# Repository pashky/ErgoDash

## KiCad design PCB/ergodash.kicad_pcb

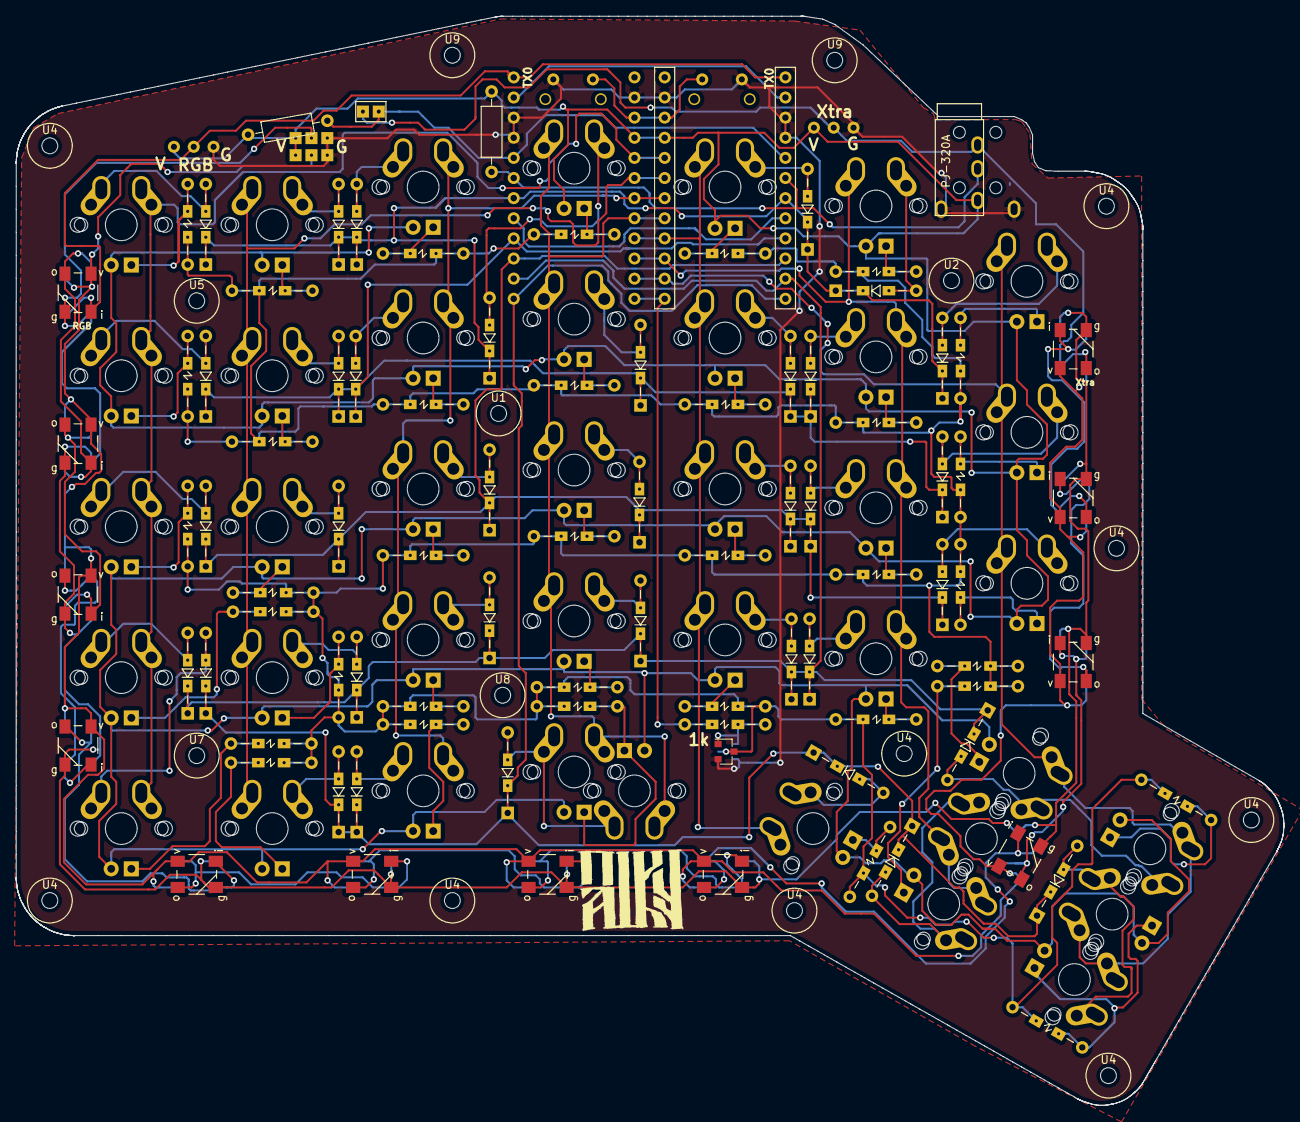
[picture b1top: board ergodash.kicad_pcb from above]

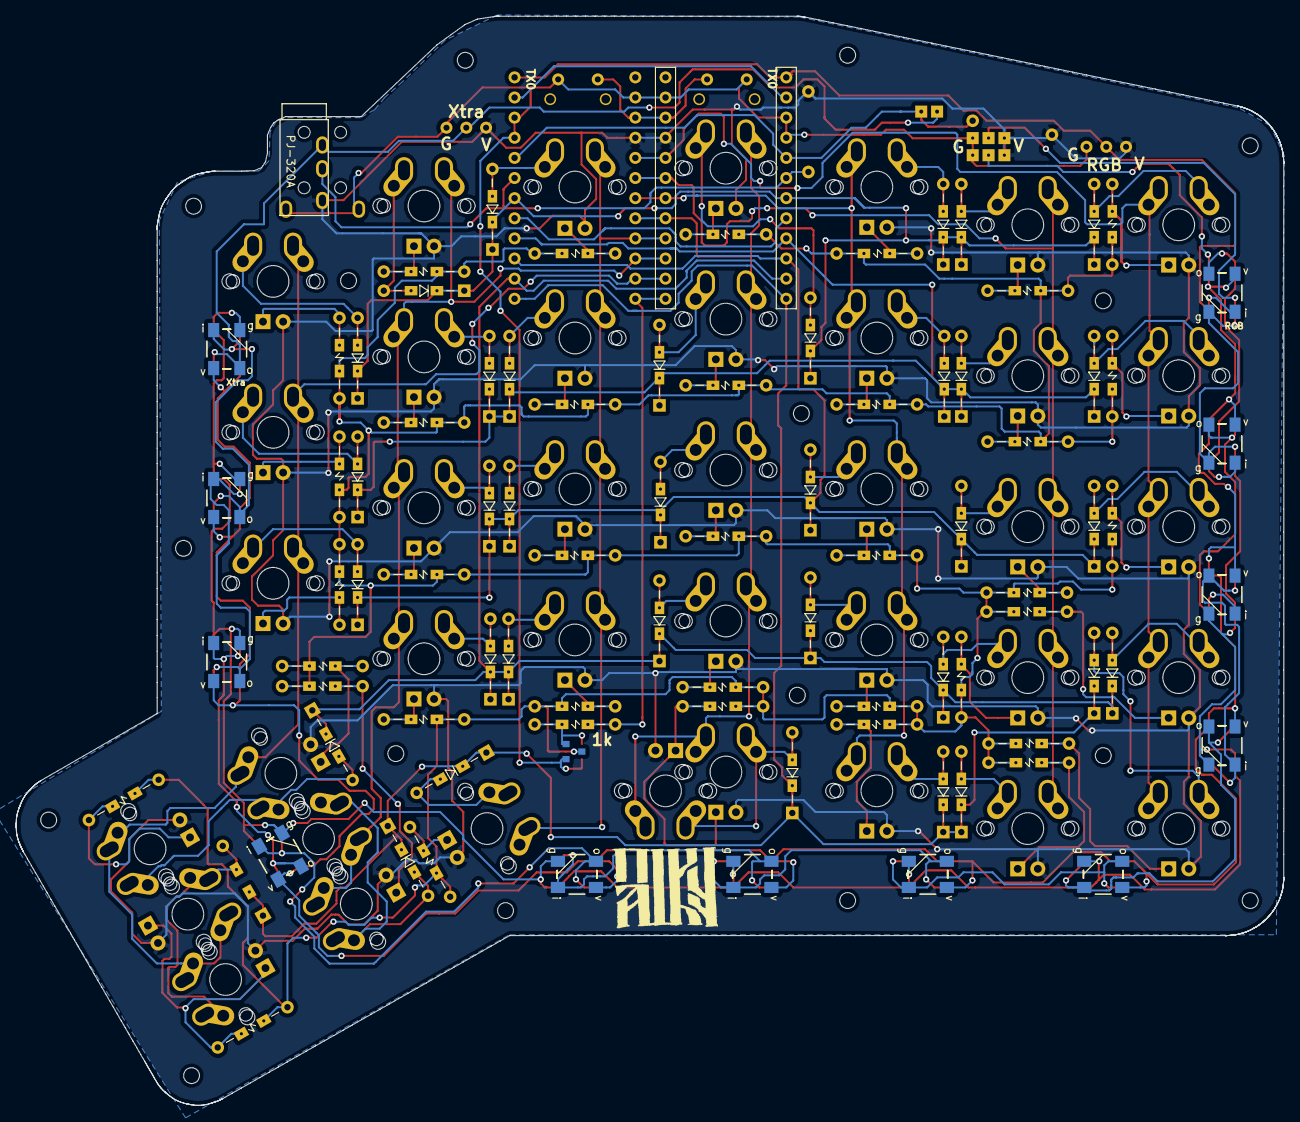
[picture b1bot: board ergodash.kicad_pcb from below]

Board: 2 copper layers, 160.0 x 137.5 mm, 190 parts (26 on the bottom side), 108 nets.

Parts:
D1, D2, D3, D4, D5, D6, D7, D8, D9, D10, D11, D12, D13, D14, D15, D16, D17, D18, D19, D20, D21, D22, D23, D24, D25, D26, D27, D28, D29, D30, D31, D32, D33, D34: D; Diode_SMD_THT3
D35, D36, D37, D38, D39, D40, D41, D42, D43, D44, D45, D46, D47, D48, D49, D50, D51, D52, D53, D54, D55, D56, D57, D58, D59, D60, D61, D62, D63, D64, D65, D66, D67, D69, D70, D71, D72, D73: LED; CHERRY_MX_LED2
D68: D; Diode_SMD_THT2
J1: 5PIN; TRRS-PJ-320A-dual
J2, J3: Conn_01x03; conn3
J4, J5: GS3; jumper2
LED1, LED2, LED3, LED4, LED5, LED6, LED7, LED8, LED9, LED10, LED11, LED12: WS2812B; WS2812B-5
Q1: IRLML6344TRPbF; SOT-23_2
R1, R2: R; R_Axial_DIN0207_L6.3mm_D2.5mm_P10.16mm_Horizontal
R3, R4, R5, R6, R7, R8, R9, R10, R11, R12, R14, R15, R16, R17, R18, R19, R20, R21, R22, R23, R24, R25, R26, R27, R28, R29, R30, R31, R32, R33, R34, R35, R36, R37, R38, R39: R; Resistors_SMD_THT
R13: 1k; Resistors_SMD_THT
SW1, SW2, SW3, SW4, SW5, SW6, SW7, SW8, SW9, SW10, SW11, SW12, SW13, SW14, SW15, SW16, SW17, SW18, SW19, SW20, SW21, SW22, SW23, SW24, SW25, SW26, SW27, SW28, SW30, SW31, SW32, SW33, SW34, SW35, SW36, SW38, SW39, SW40, SW41: SW_PUSH; MX_ALPS
SW29, SW37: SW_Push; tact_switch2
U1, U2, U4, U4#2, U4#3, U4#4, U4#5, U4#6, U4#7, U4#8, U4#9, U5, U7, U8, U9, U9#2: HOLE; hole
U3, U6: ProMicro; ProMicro_rev
W1: jumper_smd; jumper_smd_2dub

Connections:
/Audio: U3.8, U6.8
/Backlight: R13.1, U3.13, U6.13
/RBG: J2.2, LED1.2, U3.1, U6.1
/RX: U3.2, U6.2
/col0: SW1.1, SW2.1, SW3.1, SW4.1, SW30.1, U3.20, U6.20
/col1: SW5.1, SW6.1, SW7.1, SW8.1, SW31.1, U3.19, U6.19
/col2: SW9.1, SW10.1, SW11.1, SW12.1, SW32.1, U3.18, U6.18
/col3: SW13.1, SW14.1, SW15.1, SW16.1, SW33.1, SW38.1, U3.17, U6.17
/col4: SW17.1, SW18.1, SW19.1, SW20.1, SW34.1, U3.16, U6.16
/col5: SW21.1, SW22.1, SW23.1, SW24.1, SW35.1, SW36.1, U3.15, U6.15
/col6: SW25.1, SW26.1, SW27.1, SW28.1, SW39.1, SW40.1, SW41.1, U3.14, U6.14
/row0: D1.1, D5.1, D9.1, D13.1, D17.1, D21.1, D25.1, U3.7, U6.7
/row1: D2.1, D6.1, D10.1, D14.1, D18.1, D22.1, D26.1, U3.9, U6.9
/row2: D3.1, D7.1, D11.1, D15.1, D19.1, D23.1, D27.1, U3.10, U6.10
/row3: D4.1, D8.1, D12.1, D16.1, D20.1, D24.1, D28.1, U3.11, U6.11
/row4: D29.1, D30.1, D31.1, D32.1, D33.1, D34.1, D68.1, U3.12, U6.12
/rst: SW29.1, SW37.1, U3.22, U6.22
/scl: R1.2, U3.5, U6.5, W1.2
/sda/uart: J1.3, R2.2, U3.6, U6.6
/xtradata: J1.2, J3.2, LED12.4, W1.1
GND: J1.4, J1.5, J2.3, J3.3, J4.3, J5.3, Q1.2, SW29.2, SW37.2, U3.3, U3.4, U3.23, U6.3, U6.4, U6.23
unnamed: D1.2, SW1.2
unnamed: D2.2, SW2.2
unnamed: D3.2, SW3.2
unnamed: D4.2, SW4.2
unnamed: D5.2, SW5.2
unnamed: D6.2, SW6.2
unnamed: D7.2, SW7.2
unnamed: D8.2, SW8.2
unnamed: D9.2, SW9.2
unnamed: D10.2, SW10.2
unnamed: D11.2, SW11.2
unnamed: D12.2, SW12.2
unnamed: D13.2, SW13.2
unnamed: D14.2, SW14.2
unnamed: D15.2, SW15.2
unnamed: D16.2, SW16.2
unnamed: D17.2, SW17.2
unnamed: D18.2, SW18.2
unnamed: D19.2, SW19.2
unnamed: D20.2, SW20.2
unnamed: D21.2, SW21.2
unnamed: D22.2, SW22.2
unnamed: D23.2, SW23.2
unnamed: D24.2, SW24.2
unnamed: D25.2, SW25.2
unnamed: D26.2, SW26.2
unnamed: D27.2, SW27.2
unnamed: D28.2, SW28.2, SW39.2
unnamed: D29.2, SW30.2
unnamed: D30.2, SW31.2
unnamed: D31.2, SW32.2
unnamed: D32.2, SW33.2, SW38.2
unnamed: D33.2, SW34.2
unnamed: D34.2, SW35.2, SW36.2
unnamed: D35.1, R3.1
unnamed: D36.1, R4.1
unnamed: D37.1, R5.1
unnamed: D38.1, R6.1
unnamed: D39.1, R7.1
unnamed: D40.1, R8.1
unnamed: D41.1, R9.1
unnamed: D42.1, R10.1
unnamed: D43.1, R11.1
unnamed: D44.1, R12.1
unnamed: D45.1, R15.1
unnamed: D46.1, R16.1
unnamed: D47.1, R17.1
unnamed: D48.1, R18.1
unnamed: D49.1, R19.1
unnamed: D50.1, R20.1
unnamed: D51.1, R21.1
unnamed: D52.1, R22.1
unnamed: D53.1, R23.1
unnamed: D54.1, R24.1
unnamed: D55.1, R25.1
unnamed: D56.1, R26.1
unnamed: D57.1, R27.1
unnamed: D58.1, R28.1
unnamed: D59.1, R29.1
unnamed: D60.1, R30.1
unnamed: D61.1, R31.1
unnamed: D62.1, R32.1
unnamed: D63.1, R33.1
unnamed: D64.1, R34.1
unnamed: D65.1, R35.1
unnamed: D66.1, D67.1, R36.1
unnamed: D68.2, SW40.2, SW41.2
unnamed: D69.1, R14.1
unnamed: D70.1, R37.1
unnamed: D71.1, R38.1
unnamed: D72.1, D73.1, R39.1
unnamed: J4.2, LED1.1, LED2.1, LED3.1, LED4.1, LED5.1, LED6.1, LED7.1, LED8.1, LED9.1, LED10.1, LED11.1, LED12.1
unnamed: J5.2, LED1.3, LED2.3, LED3.3, LED4.3, LED5.3, LED6.3, LED7.3, LED8.3, LED9.3, LED10.3, LED11.3, LED12.3
unnamed: LED1.4, LED2.2
unnamed: LED2.4, LED3.2
unnamed: LED3.4, LED4.2
unnamed: LED4.4, LED5.2
unnamed: LED5.4, LED6.2
unnamed: LED6.4, LED7.2
unnamed: LED7.4, LED8.2
unnamed: LED8.4, LED9.2
unnamed: LED9.4, LED10.2
unnamed: LED10.4, LED11.2
unnamed: LED11.4, LED12.2
unnamed: Q1.1, R13.2
unnamed: Q1.3, R3.2, R4.2, R5.2, R6.2, R7.2, R8.2, R9.2, R10.2, R11.2, R12.2, R14.2, R15.2, R16.2, R17.2, R18.2, R19.2, R20.2, R21.2, R22.2, R23.2, R24.2, R25.2, R26.2, R27.2, R28.2, R29.2, R30.2, R31.2, R32.2, R33.2, R34.2, R35.2, R36.2, R37.2, R38.2, R39.2
VCC: D35.2, D36.2, D37.2, D38.2, D39.2, D40.2, D41.2, D42.2, D43.2, D44.2, D45.2, D46.2, D47.2, D48.2, D49.2, D50.2, D51.2, D52.2, D53.2, D54.2, D55.2, D56.2, D57.2, D58.2, D59.2, D60.2, D61.2, D62.2, D63.2, D64.2, D65.2, D66.2, D67.2, D69.2, D70.2, D71.2, D72.2, D73.2, J1.1, J2.1, J3.1, J4.1, J5.1, R1.1, R2.1, U3.21, U6.21

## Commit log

2018-07-13 My adpatations added
    - Changed TRRS jack to PJ-320A
    - Added border and holes for sandwich plateless case
